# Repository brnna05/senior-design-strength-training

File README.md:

# senior-design-strength-training
Senior Design project for ECE 364D - Fitness wearable for strength training

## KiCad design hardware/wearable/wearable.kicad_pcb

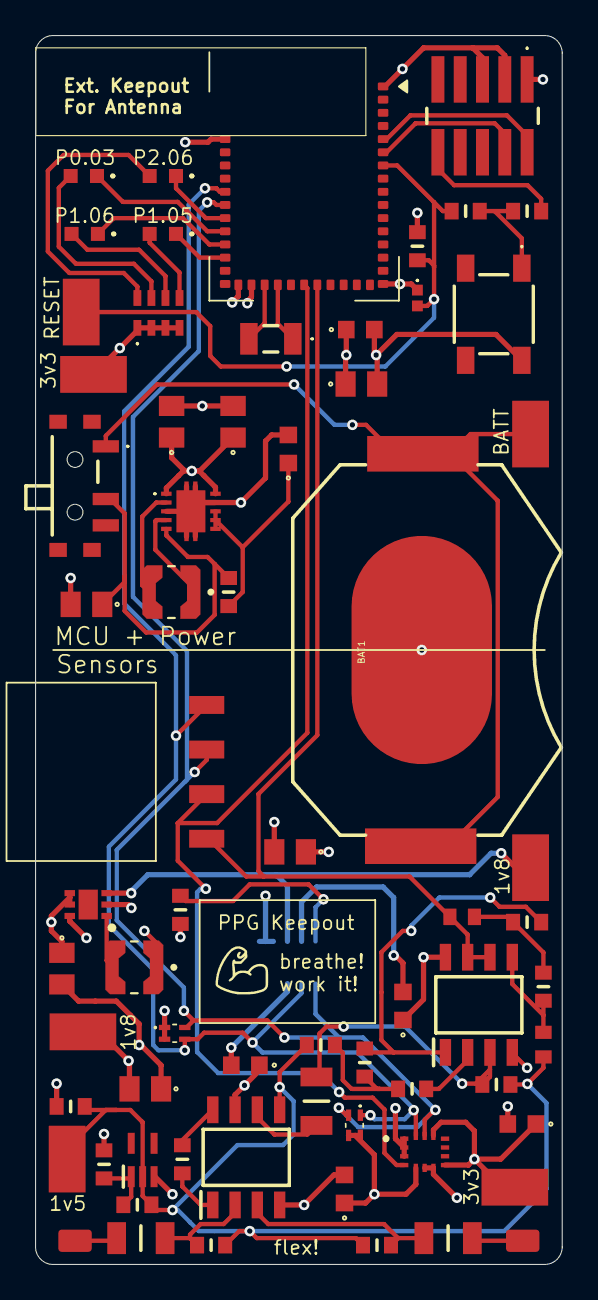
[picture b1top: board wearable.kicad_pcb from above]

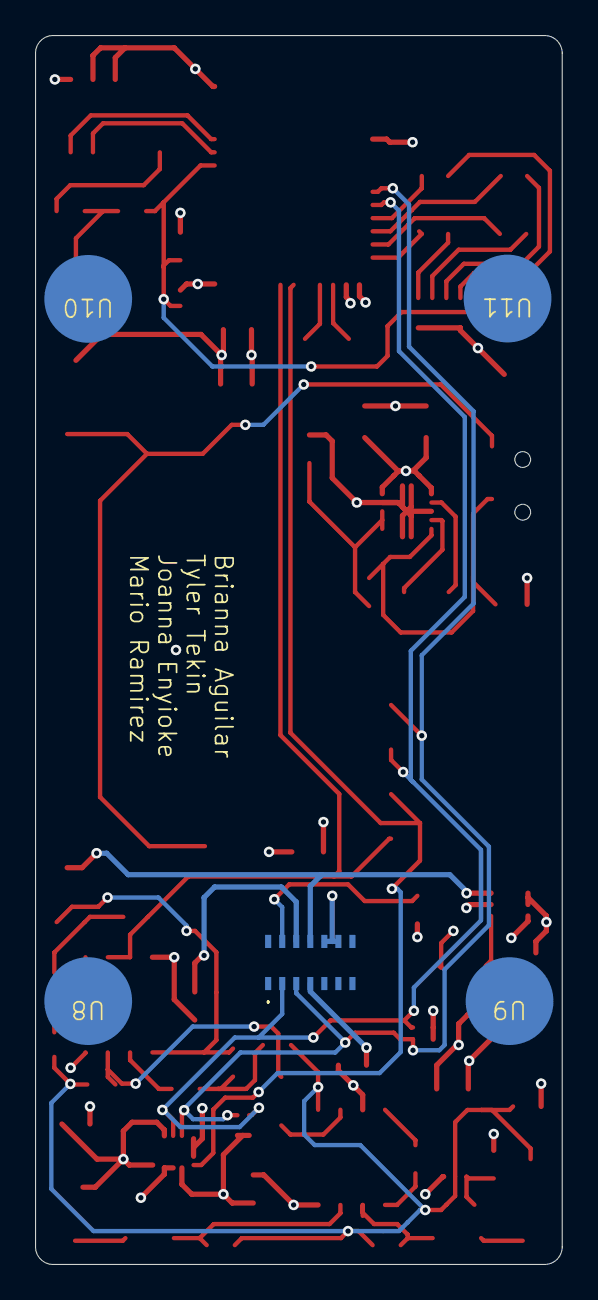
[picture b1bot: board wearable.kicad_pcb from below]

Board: 4 copper layers, 30.0 x 70.0 mm, 72 parts (5 on the bottom side), 44 nets.

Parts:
BAT1: 20mm coincell; batteryHolder
C9: 100nF; ceramicCap0_1uF
C10, C16, C17, C18, C19, C22, C23: 10uF; ceramicCap10uF
C11: 3.9pF; ceramicCap3_9pF
C12, C13, C15: 0.1uF; C0GCap0_1uF
C14, C20, C21, C26, C27: 0.1uF; ceramicCap0_1uF
C24, C25: 0.01uF; C0GCap0_01uF
D1, D2, D3, D4: LED; greenLed
IC1: LM4041CILPR; lm4041
IC2: INA828IDR; ina828
IC3: MAX30102EFD+T; ppg
IC4: TPS63001DRCT; boost3_3v
IC5: OPA2350UA; opAmp
IC6: TPS62293DRVR; buck1_8v
J1: Conn_02x05_Odd_Even; swdConnector
J2: Conn_01x04_Pin; pinHeader1x4
L1, L2: 2.2uH; inductor
R11: 2.7k; res2K7
R12, R14, R24: 4.7k; res4K7
R13, R20, R27: 100; res100
R15, R22: 1k; res1K
R16, R17: 100k; res100K
R18: 5.6k; res5K6
R19, R21: 1M; res1M
R23: 200k; res200K
R25, R26: 47k; red47K
RN1: 470; resArray4
RN2, RN3: 4.7k; resArray2
SW1: SW_Push; button
SW2: SW_SPDT; spdt
TP1, TP2, TP3, TP4, TP5, TP6, TP7: TestPoint; testPoint
U4: BL54L15-453-000xxx; BL54Lxx-LGA-39_14x10mm
U5: LSM6DSOTR; imu
U6, U7: silverContacts
U8, U9, U10, U11: solderPad
Y3: NX3215SA-32.768K-STD-MUA-8; crystal32768

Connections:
+1V8: C22.2, IC3.11 (VDD), IC6.3 (FB), L2.1, TP5.1, TP6.1
+3V3: C9.1, C10.1, C14.1, C17.1, C18.1, C19.1, C21.1, C23.2, C26.1, C27.1, IC2.7 (+VS), IC3.9 (VLED+_1), IC3.10 (VLED+_2), IC4.1 (VOUT), IC4.10 (FB), IC5.8 (V+), IC6.4 (EN), IC6.5 (VIN), J1.1, R11.1, R12.1, R24.1, RN1.1, RN1.2, RN1.3, RN1.4, RN2.1, RN2.2, RN3.3, RN3.4, TP4.1, TP7.1, U4.26 (VDD), U5.5 (VDDIO), U5.8 (VDD), U5.12 (CS)
GND: BAT1.NEGATIVE (-), C9.2, C10.2, C11.1, C14.2, C16.2, C17.2, C18.2, C19.2, C20.2, C21.2, C22.1, C23.1, C26.2, C27.2, IC1.3, IC2.4 (-VS), IC3.4 (PGND), IC3.12 (GND), IC4.3 (PGND_1), IC4.9 (GND), IC4.11 (PGND_2), IC4.12 (PGND_3), IC4.13 (PGND_4), IC4.14 (PGND_5), IC4.15 (PGND_6), IC5.4 (V-), IC6.2 (MODE), IC6.6 (GND), J1.3, J1.5, R15.2, SW1.2, U4.1 (VSS), U4.16 (VSS), U4.27 (VSS), U4.39 (VSS), U5.1 (SDO/SA0), U5.2 (SDx), U5.3 (SCx), U5.6 (GND), U5.7 (GND)
unnamed: C12.1, U6.1
unnamed: C13.1, U7.1
unnamed: C24.2, R25.2, R26.1
unnamed: D1.2 (A), RN1.8
unnamed: D2.2 (A), RN1.7
unnamed: D3.2 (A), RN1.6
unnamed: D4.2 (A), RN1.5
unnamed: IC1.1, R14.2, R15.1
unnamed: C13.2, IC2.3 (+IN), R17.2
unnamed: C12.2, IC2.2 (-IN), R16.1
unnamed: C15.1, IC2.6 (OUT)
unnamed: C25.1, IC1.2, IC2.5 (REF), R11.2, R14.1, R16.2, R17.1, R19.2, R22.2, TP2.1
unnamed: IC2.1 (RG_1), R18.1
unnamed: IC2.8 (RG_2), R18.2
unnamed: IC3.13 (~INT), R24.2
unnamed: C20.1, IC4.6 (EN), IC4.7 (PS/SYNC), IC4.8 (VINA), R20.2
unnamed: IC4.4 (L1), L1.1
unnamed: IC4.2 (L2), L1.2
unnamed: C16.1, IC4.5 (VIN), R20.1, SW2.2 (B)
unnamed: C15.2, IC5.3 (+IN_A), R19.1
unnamed: C25.2, IC5.5 (+IN_B), R26.2
unnamed: IC5.2 (-IN_A), R21.1
unnamed: IC5.1 (OUT_A), R23.2, R25.1
unnamed: IC6.1 (SW), L2.2
unnamed: J1.10, R27.1
unnamed: R21.2, R22.1, R23.1
unnamed: BAT1.POSITIVE@1 (+), BAT1.POSITIVE@2 (+), BAT1.POSITIVE@3 (+), BAT1.POSITIVE@4 (+), SW2.1 (A), TP3.1
unnamed: U4.25 (P1.00), Y3.2 (CRYSTAL_2)
unnamed: U4.24 (P1.01), Y3.1
unnamed: C11.2, R12.2, R13.1, TP1.1, U4.7 (~RESET)
P0.04: D3.1 (K), U4.31 (P0.04)
P1.05: J2.2, U4.22 (P1.05), U5.4 (INT1)
P1.06: C24.1, IC5.6 (-IN_B), IC5.7 (OUT_B), J2.1, U4.21 (P1.06)
P1.08: D4.1 (K), U4.30 (P1.08)
P1.11: IC3.3 (SDA), J2.4, RN2.3, RN3.1, U4.35 (P1.11), U5.14 (SDA)
P1.12: IC3.2 (SCL), J2.3, RN2.4, RN3.2, U4.34 (P1.12), U5.13 (SCL)
P1.13: D1.1 (K), U4.33 (P1.13)
P1.14: D2.1 (K), U4.32 (P1.14)
SWDCLK: J1.4, U4.6 (SWDCLK)
SWDIO: J1.2, U4.5 (SWDIO)
~RESET: R13.2, R27.2, SW1.1

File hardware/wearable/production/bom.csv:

Designator,Footprint,Quantity,Value,LCSC Part #
BAT1,batteryHolder,1,20mm coincell,
"C10, C16, C17, C18, C19, C22, C23",ceramicCap10uF,7,10uF,
C11,ceramicCap3_9pF,1,3.9pF,
"C12, C13, C15",C0GCap0_1uF,3,0.1uF,
"C14, C20, C21, C26, C27",ceramicCap0_1uF,5,0.1uF,
"C24, C25",C0GCap0_01uF,2,0.01uF,
C9,ceramicCap0_1uF,1,100nF,
"D1, D2, D3, D4",greenLed,4,LED,
IC1,lm4041,1,LM4041CILPR,
IC2,ina828,1,INA828IDR,
IC3,ppg,1,MAX30102EFD+T,
IC4,boost3_3v,1,TPS63001DRCT,
IC5,opAmp,1,OPA2350UA,
IC6,buck1_8v,1,TPS62293DRVR,
J1,swdConnector,1,Conn_02x05_Odd_Even,
J2,pinHeader1x4,1,Conn_01x04_Pin,
"L1, L2",inductor,2,2.2uH,
R11,res2K7,1,2.7k,
"R12, R14, R24",res4K7,3,4.7k,
"R13, R20, R27",res100,3,100,
"R15, R22",res1K,2,1k,
"R16, R17",res100K,2,100k,
R18,res5K6,1,5.6k,
"R19, R21",res1M,2,1M,
R23,res200K,1,200k,
"R25, R26",red47K,2,47k,
RN1,resArray4,1,470,
"RN2, RN3",resArray2,2,4.7k,
SW1,button,1,SW_Push,
SW2,spdt,1,SW_SPDT,
"TP1, TP2, TP3, TP4, TP5, TP6, TP7",testPoint,7,TestPoint,
"U10, U11, U8, U9",solderPad,4,~,
U4,BL54Lxx-LGA-39_14x10mm,1,BL54L15-453-000xxx,
U5,imu,1,LSM6DSOTR,
"U6, U7",silverContacts,2,~,
Y3,crystal32768,1,NX3215SA-32.768K-STD-MUA-8,

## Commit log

2025-10-28 setup
2025-11-03 emg module-- subject to change
2025-12-29 minimal histoy page set up
2026-01-15 wireframes
2026-02-02 updated kicad again..
2026-02-02 rework app and set up navigation
2026-02-03 history and settings page
2026-02-03 add svg icons
2026-02-04 init app for nrf54
2026-02-04 it builds ig
2026-02-13 zephyr adc_sequence example
2026-02-14 adc module for csv data collection
2026-02-15 update adc to be a timer ISR
2026-02-16 hardware so far
2026-02-16 data logging instructions
2026-02-16 schematic and bom are complete
2026-02-18 working on 3x8cm pcb
2026-02-18 team data
2026-02-22 plots
2026-03-02 interactive live session dummy
2026-03-02 full history and live workout
2026-03-02 i2c ports to be 1.11/12 and ppg can communicate via ir readings. working to implement ble and working imu in tandem with ppg
2026-03-02 login + persistent history
2026-03-04 messing with submodules
2026-03-04 add imu/ppg
2026-03-04 PROPERLY messing with git submodules, why does cmake hate long path names???
2026-03-04 removal fp
2026-03-04 imu set up w/ adc
2026-03-04 REVERT TO THIS IS HARDWARE GOES TO SHIT
2026-03-04 data with imu/ppg
2026-03-10 ahhhhhhhhhhhhhhhhhhhhhhh firmware is no longer a submodule per peer request... thanks brianna...
2026-03-10 this is annoying
2026-03-10 removed nested .git file
2026-03-11 data from 03/11
2026-03-11 update: data info format
2026-03-15 main does the printing
2026-03-15 clean hw folder
2026-03-22 add sides and logo
2026-03-23 Update rtt_log_20260311_140558.csv
    Removed heart rate lines. "MAX...heart rate = 75 BPM"
2026-03-29 rahh BLE works on mcu and phone
2026-04-15 add insights to live workout
2026-04-22 ml stuff
2026-04-26 ble+ppg on pcb work, imu doesn't
2026-04-26 fix imu on pcb, need to fix adc
2026-04-26 i lied adc works but imu doesn't
2026-04-27 working when rms is low
